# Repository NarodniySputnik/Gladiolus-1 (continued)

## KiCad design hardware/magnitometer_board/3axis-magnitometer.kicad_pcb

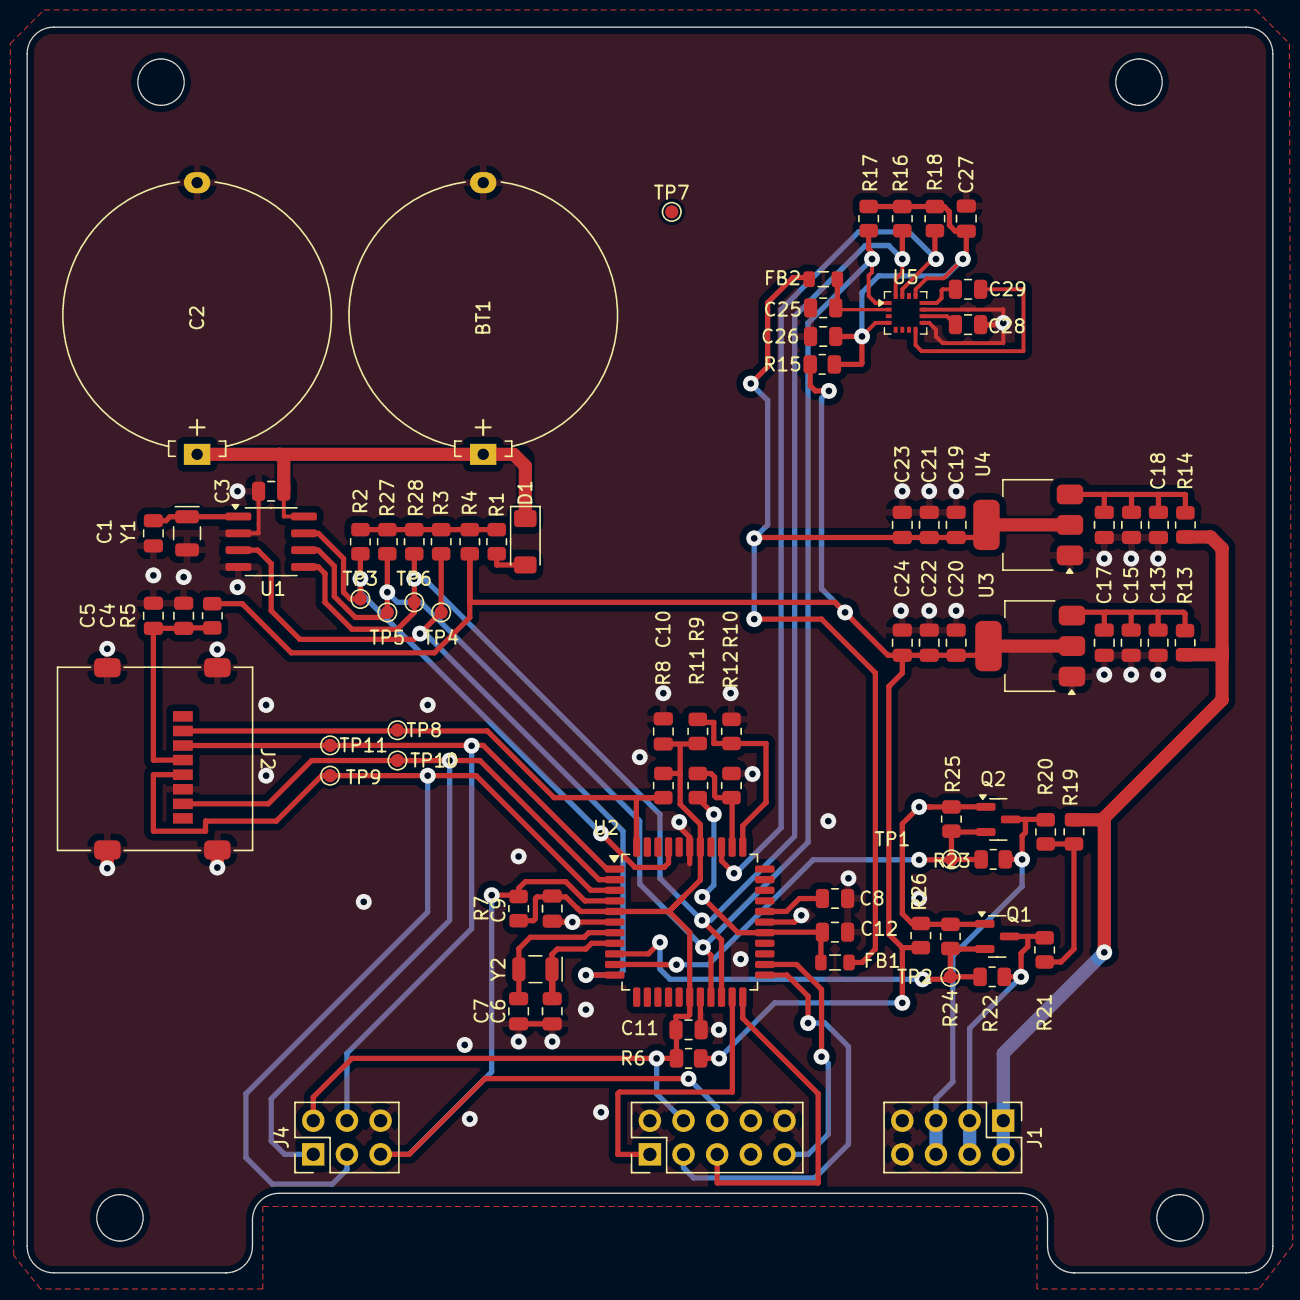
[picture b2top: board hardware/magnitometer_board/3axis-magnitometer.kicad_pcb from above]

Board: 2 copper layers, 94.0 x 94.0 mm, 85 parts (0 on the bottom side), 43 nets.

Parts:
BT1: Battery_Cell; Battery_Panasonic_CR2032-HFN_Horizontal_CircularHoles
C1, C6, C7: 22p; C_0805_2012Metric
C2: C_Polarized; Battery_Panasonic_CR2032-HFN_Horizontal_CircularHoles
C3: 0.1; C_0805_2012Metric
C4, C8, C9, C10, C11, C12, C25, C26, C27, C29: 0.22; C_0805_2012Metric
C5: 100p; C_0805_2012Metric
C13, C14, C15, C16, C21, C22, C23, C24: C; C_0805_2012Metric
C17, C18, C19, C20, C28: 4.7; C_0805_2012Metric
D1: LL42; D_MiniMELF
FB1, FB2: FerriteBead; L_0805_2012Metric
J1: Conn_01x08_Pin; PinHeader_2x04_P2.54mm_Vertical
J2: Micro_SD_Card; microSD_HC_Molex_47219-2001
J3: AVR-JTAG-10; PinHeader_2x05_P2.54mm_Vertical
J4: AVR-ISP-6; PinHeader_2x03_P2.54mm_Vertical
Q1, Q2: BSS138; SOT-23
R1, R4, R5, R6, R15, R19, R26: 10; R_0805_2012Metric
R2, R3, R7, R8, R9, R10, R11, R12, R16, R17, R18, R20, R21, R24, R25, R27, R28: 2.2k; R_0805_2012Metric
R13, R14: 1; R_0805_2012Metric
R22, R23: 0; R_0805_2012Metric
TP1, TP2, TP3, TP4, TP7, TP8, TP9, TP10, TP11: TestPoint; TestPoint_Pad_D1.0mm
TP5: SCL; TestPoint_Pad_D1.0mm
TP6: SDA; TestPoint_Pad_D1.0mm
U1: PCF8563T; SOIC-8_3.9x4.9mm_P1.27mm
U2: ATmega32A-A; TQFP-44_10x10mm_P0.8mm
U3, U4: AMS1117-3.3; SOT-223-3_TabPin2
U5: qmc5883l; LGA-16_3x3mm_P0.5mm
Y1: 32.768кГц; Crystal_SMD_EuroQuartz_EQ161-2Pin_3.2x1.5mm
Y2: 7.3728MHz; Crystal_SMD_EuroQuartz_EQ161-2Pin_3.2x1.5mm

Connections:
+3.3V: C20.1, C22.1, C24.1, R4.2, R5.1, R6.1, R15.1, R26.2, U3.2 (VO)
+3.3VA: C19.1, C21.1, C23.1, FB1.1, FB2.1, U4.2 (VO)
+5V: J1.1, J1.2, R13.1, R14.1, R19.1
/CLK0: R2.2, TP3.1, U1.7 (CLKO), U2.41 (PB1)
/DRDY: R18.2, TP7.1, U2.36 (PA1), U5.15 (DRDY)
/INT: R3.2, TP4.1, U1.3 (~INT), U2.11 (PD2)
/MISO: J2.7 (DAT0), J4.1 (MISO), TP10.1, U2.2 (PB6)
/MOSI: J2.3 (CMD), J4.4 (MOSI), TP11.1, U2.1 (PB5)
/SCK: J2.5 (CLK), J4.3 (SCK), TP9.1, U2.3 (PB7)
/SCL: R17.2, R27.2, TP5.1, U1.6 (SCL), U2.19 (PC0), U5.1 (SCL)
/SDA: R16.2, R28.2, TP6.1, U1.5 (SDA), U2.20 (PC1), U5.16 (SDA)
/SS: J2.2 (DAT3/CD), R8.2, TP8.1, U2.44 (PB4)
/level_translator/RX: J1.3, J1.4, Q1.3 (D), R21.2, R22.1
/level_translator/TX: J1.5, J1.6, Q2.3 (D), R20.2, R23.1
/level_translator/UART_RX: Q1.2 (S), R22.2, R24.2, TP2.1, U2.9 (PD0)
/level_translator/UART_TX: Q2.2 (S), R23.2, R25.2, TP1.1, U2.10 (PD1)
/mc/TCK: J3.1 (TCK), U2.21 (PC2)
/mc/TDI: J3.9 (TDI), U2.24 (PC5)
/mc/TDO: J3.3 (TDO), U2.23 (PC4)
/mc/TMS: J3.5 (TMS), U2.22 (PC3)
/mc/~RESET: J3.6 (~SRST), J4.5 (~RST), R7.2, U2.4 (~RESET)
GND: BT1.2 (-), C1.2, C2.2, C3.1, C4.1, C5.1, C6.2, C7.2, C8.1, C9.1, C10.1, C11.1, C12.2, C13.2, C14.2, C15.2, C16.2, C17.2, C18.2, C19.2, C20.2, C21.2, C22.2, C23.2, C24.2, C25.2, C26.2, C27.2, C28.2, J1.7, J1.8, J2.6 (VSS), J2.9 (SHIELD), J3.2 (GND), J3.10 (GND), J4.6 (GND), R10.2, R12.2, U1.2 (OSCO), U1.4 (VSS), U2.6 (GND), U2.18 (GND), U2.28 (GND), U2.39 (GND), U3.1 (GND), U4.1 (GND), U5.9 (VSS), U5.11 (VSS), Y1.2
unnamed: BT1.1 (+), C2.1, C3.2, D1.1 (K), U1.8 (VDD)
unnamed: D1.2 (A), R1.1
unnamed: C4.2, C5.2, J2.4 (VDD), R5.2
unnamed: C9.2, C10.2, C11.2, J3.4 (VREF), J4.2 (VCC), R6.2, R7.1, R8.1, R9.1, U2.5 (VCC), U2.17 (VCC), U2.38 (VCC)
unnamed: Q1.1 (G), Q2.1 (G), R24.1, R25.1, R26.1
unnamed: R1.2, R2.1, R3.1, R4.1, R27.1, R28.1
unnamed: R19.2, R20.1, R21.1
unnamed: C1.1, U1.1 (OSCI), Y1.1
unnamed: C8.2, U2.29 (AREF)
unnamed: C12.1, FB1.2, R11.1, U2.27 (AVCC)
unnamed: R11.2, R12.1, U2.35 (PA2)
unnamed: R9.2, R10.1, U2.34 (PA3)
unnamed: C6.1, U2.8 (XTAL1), Y2.1
unnamed: C7.1, U2.7 (XTAL2), Y2.2
unnamed: C13.1, C15.1, C17.1, R13.2, U3.3 (VI)
unnamed: C14.1, C16.1, C18.1, R14.2, U4.3 (VI)
unnamed: C25.1, FB2.2, U5.2 (AVDD)
unnamed: C28.1, U5.10 (C1)
unnamed: C29.2, U5.8 (CAD0)
unnamed: C29.1, U5.12 (CAD1)
unnamed: C26.1, C27.1, R15.2, R16.1, R17.1, R18.1, U5.4 (VPP), U5.13 (DVDD)

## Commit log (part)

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2025-10-15 первое тз под правки
2025-10-15 Update README.md
    Изменение требований электропитания
2025-10-15 Update README.md
    конкретизированы требования к радиоканалу
2025-10-15 Update README.md
    дополнения тз функциональное и радиомодуль
2025-10-15 Update README.md
    частота сств
2025-10-15 Update README.md
    добавил конкретики и вопросов
2025-10-15 Update README.md
    конкретизация параметров
2025-10-15 фикс форматирования
2025-10-15 Up/Dw link
2025-10-16 kicad init
2025-10-16 gitignore fix
2025-10-16 structure update
2025-10-16 structure improvements
2025-10-16 добавлены шаблоны плат
    макетные платы от ранних проектов нужно переработать в шаблоны
2025-10-16 removed all unused holes
2025-10-16 another one structure improvements
2025-10-16 again
2025-10-16 add boards req
2025-10-17 Create LICENSE
2025-10-17 Update LICENSE
2025-10-17 logotip
2025-10-17 продолжаем сохранять порядок
2025-10-17 renamed .pdf files
2025-10-17 renamed files
2025-10-17 library changes
2025-10-17 symbol update
2025-10-17 AB-IOT-433 footprint
2025-10-17 Update README.md
    актуализация изменений
2025-10-17 suggustions components
2025-10-18 updated common library
2025-10-18 Update README.md
    убрал модуль управления. вме делает материнская плата
2025-10-18 Добавил плату магнитометра
    Добавил плату магнитометра
2025-10-18 renamed .txt file
2025-10-18 little changes
2025-10-18 let's gooo
2025-10-18 yeeeeah
2025-10-18 removed to follow .gitignore
2025-10-18 renamed datasheet to ds
2025-10-18 removed underscore from library folder name
2025-10-18 another renaming
2025-10-20 raspberry pi zero symbol
2025-10-20 updated library structure
2025-10-20 подпапки в DS
2025-10-20 1-wire микросхемы добавлены
2025-10-20 1-wire update ic list
2025-10-20 little fixes
2025-10-20 Update README.md выбрана микросхема супервизора питания
2025-10-20 Create MAX6301.pdf
    выбрана микросхема супервизора основного питания
2025-10-20 Update README.md
    супервизор питания
2025-10-20 removed unused pins on template schematic
2025-10-21 add UC
2025-10-21 add command list
2025-10-21 crct grammar_err
2025-10-22 Create .gitkeep
    Create Antenna module components datasheet folder.
2025-10-22 Create iinfo developers, technical staff
2025-10-22 Update iinfo developers, technical staff
    Uzzzio assign to antenna deployment mechanism
2025-10-22 Update and rename iinfo developers, technical staff to Info developers, technical staff
2025-10-23 продолжаем придерживаться структуры проекта
2025-10-28 Readme
2025-10-31 изменена структура. добавлен новый модем
2025-11-01 выбран ключ с защитой от защелкивания
2025-11-03 add magnitomet
2025-11-13 Update README.md
    Корректировка ТЗ
2025-11-13 вёрстка
2025-11-13 readme-table
2025-11-13 edit table
2025-11-14 Create требование к интегрированной системе управления питанием
    Добавлено тз на систему управления питанием
2025-11-14 Update требование к интегрированной системе управления питанием
2025-11-19 tables
2025-11-22 дарю вёрстку
2025-11-22 правка вёрстки
2025-11-23 example
2025-12-03 добавил орбитальные эмулятор
2025-12-07 Update требование к интегрированной системе управления питанием
    English translate
2026-01-06 Update README.md
    модемные блоки
2026-01-12 LTC3119
2026-02-09 и создал бог проект, и назвал его stm-sstv
2026-02-19 Fix typo in gain coefficient description
2026-02-19 Create RadioComm
2026-02-19 Add read.me file for modem board
2026-02-19 Add microcontroller information for modem to README
2026-02-19 Add files via upload
    Файлы платы RadioComm для KiCad ver 9.0
2026-02-19 Update read.me with version and component details
    Added version information and details about components.
2026-02-22 Remove @alisialightness from technical writers list
2026-02-26 начата новая трассировка
2026-02-26 Добавлен документ системной блок-схемы
2026-02-27 апдейт блок-схемы
2026-03-02 трасировка магнитометра
2026-03-02 исправил контур платы
2026-03-02 апдейт блок-схемы модемного блока
2026-03-04 Магнитометр правки
2026-03-05 Финальные правки трассировки
2026-03-05 замена микросхемы преобразователя уровня
2026-03-06 герберы и финальные правки
2026-03-06 исправления трассировки
2026-03-10 апдейт блок-схемы. Часть материнского блока
2026-04-07 релиз
